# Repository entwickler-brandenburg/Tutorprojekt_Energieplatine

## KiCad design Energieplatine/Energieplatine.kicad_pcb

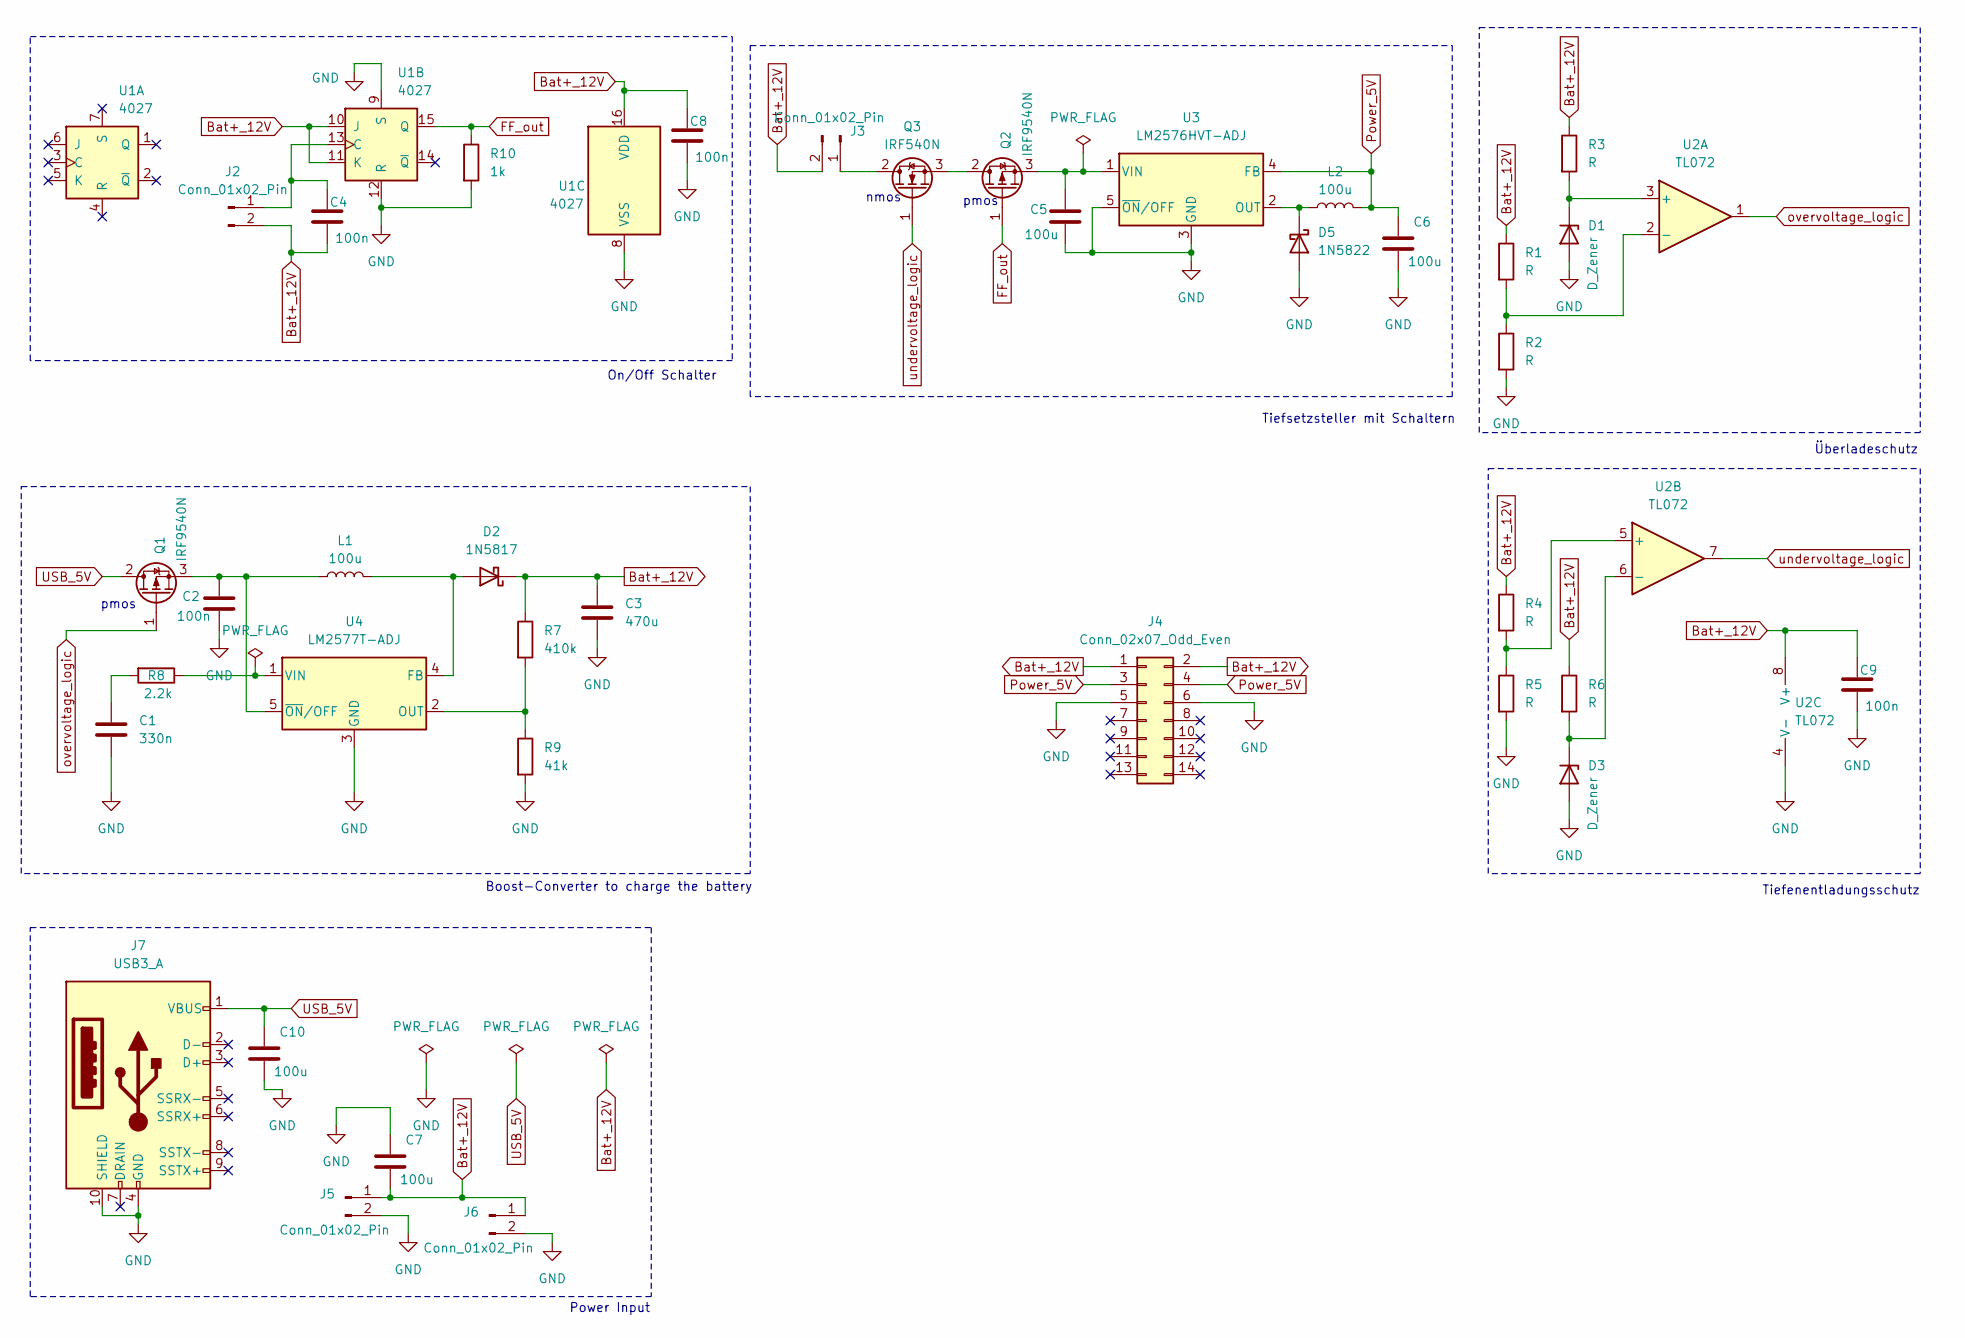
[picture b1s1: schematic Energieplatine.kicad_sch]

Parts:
C1: 330n; C_Disc_D5.0mm_W2.5mm_P2.50mm
C2, C4, C8, C9: 100n; C_Disc_D5.0mm_W2.5mm_P2.50mm
C3: 470u; C_Radial_D8.0mm_H11.5mm_P3.50mm
C5, C6, C7, C10: 100u; C_Radial_D6.3mm_H11.0mm_P2.50mm
D1, D3: D_Zener; D_A-405_P10.16mm_Horizontal
D2: 1N5817; D_DO-41_SOD81_P10.16mm_Horizontal
D5: 1N5822; D_DO-41_SOD81_P10.16mm_Horizontal
J2, J3, J5, J6: Conn_01x02_Pin; PinHeader_1x02_P2.00mm_Vertical
J4: Conn_02x07_Odd_Even; Prolab_Busstecker
J7: USB3_A; USB3_A_Molex_48393-001_short
L1, L2: 100u; L_Radial_D6.0mm_P4.00mm
Q1, Q2: IRF9540N; TO-220-3_Vertical
Q3: IRF540N; TO-220-3_Vertical
R1, R2, R3, R4, R5, R6: R; R_Axial_DIN0207_L6.3mm_D2.5mm_P7.62mm_Horizontal
R7: 410k; R_Axial_DIN0207_L6.3mm_D2.5mm_P7.62mm_Horizontal
R8: 2.2k; R_Axial_DIN0207_L6.3mm_D2.5mm_P7.62mm_Horizontal
R9: 41k; R_Axial_DIN0207_L6.3mm_D2.5mm_P7.62mm_Horizontal
R10: 1k; R_Axial_DIN0207_L6.3mm_D2.5mm_P7.62mm_Horizontal
U1: 4027; DIP-16_W7.62mm_Socket_LongPads
U2: TL072; DIP-8_W7.62mm_Socket_LongPads
U3: LM2576HVT-ADJ; TO-220-5_Vertical_Brolab
U4: LM2577T-ADJ; TO-220-5_Vertical_Brolab

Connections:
Bat+_12V: C3.1, C4.2, C7.2, C8.1, C9.1, D2.1 (K), J2.2, J3.2, J4.1, J4.2, J5.1, J6.1, R1.1, R3.1, R4.1, R6.1, R7.1, U1.10 (J), U1.11 (K), U1.16 (VDD), U2.8 (V+)
FF_out: Q2.1 (G), R10.1, U1.15 (Q)
GND: C1.2, C2.2, C3.2, C5.2, C6.2, C7.1, C8.2, C9.2, C10.2, D1.2 (A), D3.2 (A), D5.2 (A), J4.5, J4.6, J5.2, J6.2, J7.4 (GND), J7.10 (SHIELD), R2.2, R5.2, R9.2, R10.2, U1.8 (VSS), U1.9 (S), U1.12 (R), U2.4 (V-), U3.3 (GND), U3.5 (~ON/OFF), U4.3 (GND)
unnamed: C1.1, R8.2
unnamed: D1.1 (K), R3.2, U2.3 (+)
unnamed: D2.2 (A), L1.2, U4.4 (FB)
unnamed: D3.1 (K), R6.2, U2.6 (-)
unnamed: D5.1 (K), L2.1, U3.2 (OUT)
unnamed: C4.1, J2.1, U1.13 (C)
unnamed: J3.1, Q3.2 (D)
unnamed: C2.1, L1.1, Q1.3 (S), U4.5 (~ON/OFF)
unnamed: Q2.2 (D), Q3.3 (S)
unnamed: C5.1, Q2.3 (S), U3.1 (VIN)
unnamed: R1.2, R2.1, U2.2 (-)
unnamed: R4.2, R5.1, U2.5 (+)
unnamed: R7.2, R9.1, U4.2 (OUT)
unnamed: R8.1, U4.1 (VIN)
Power_5V: C6.1, J4.3, J4.4, L2.2, U3.4 (FB)
USB_5V: C10.1, J7.1 (VBUS), Q1.2 (D)
overvoltage_logic: Q1.1 (G), U2.1
undervoltage_logic: Q3.1 (G), U2.7

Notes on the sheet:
On/Off Schalter
pmos
Überladeschutz
Boost-Converter to charge the battery
Tiefsetzsteller mit Schaltern
Power Input
nmos
Tiefenentladungsschutz

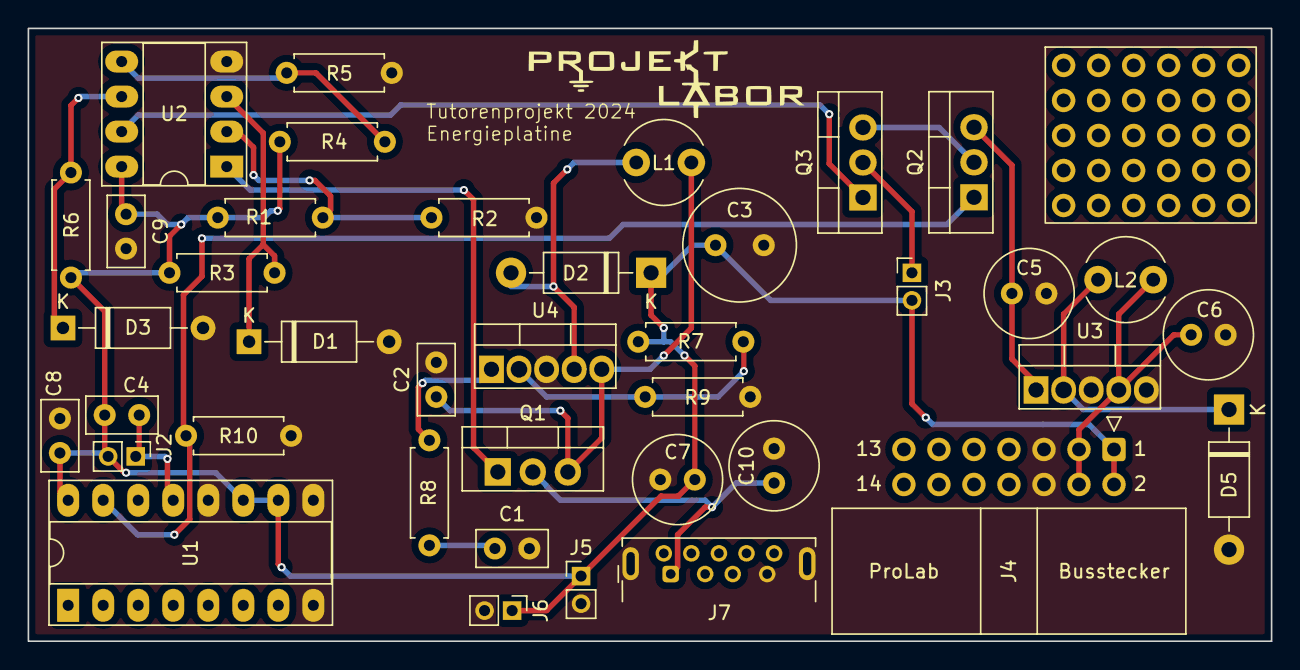
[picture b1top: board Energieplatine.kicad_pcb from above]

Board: 2 copper layers, 90.2 x 44.4 mm, 39 parts (0 on the bottom side), 21 nets.

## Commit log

2024-08-20 Basic Setup
2024-08-20 Added Resistor
2024-08-20 widerstand entfernt
2024-08-20 Added Boost-Converter
    Boost Converter to charge the battery. 5V to 13.8V
2024-08-21 Schaltung verkleinert
2024-08-24 Layout is has no DRC errors.
2024-08-25 PCB updated
    Footprints der Widerstände angepasst, daraufhin Layout der Platine angepasst.
2024-08-25 added usb-typeA
2024-08-25 asdf
2024-08-25 Added Logo on Silkscreen
    Logo und Platinenbeschriftung hinzugefügt
2024-10-06 Feedbackloop vom TSS hinzugefügt
    Spannungsteiler am Ende des TSS für die Feedbackloop hinzugefügt
2024-10-06 Platine Verbessert und Fehler gefixed
    kein Layout geupdated
